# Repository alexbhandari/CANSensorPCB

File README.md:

# Sensor to CAN Bus Remote IO PCB
Many wires in, two wires out. 24 input channels on the board interface with analog and digital sensors. Performs analog to digital to CAN protocol conversion.

## Changelog
| Release | Changes |
| --- | --- |
|  | Pre-release |

## PCB Design

- Microcontroller: RM42L432BPZT
- Input Stage: Filtering, Voltage scaling, Circuit Protection
- Output Stage: 2 Isolated CAN transceivers
- Power: 5V board power, LDO supply creates 3.3V and 1.2V

## [Code Repo](https://github.com/alexbhandari/RM42-CAN-Sensor-Code)

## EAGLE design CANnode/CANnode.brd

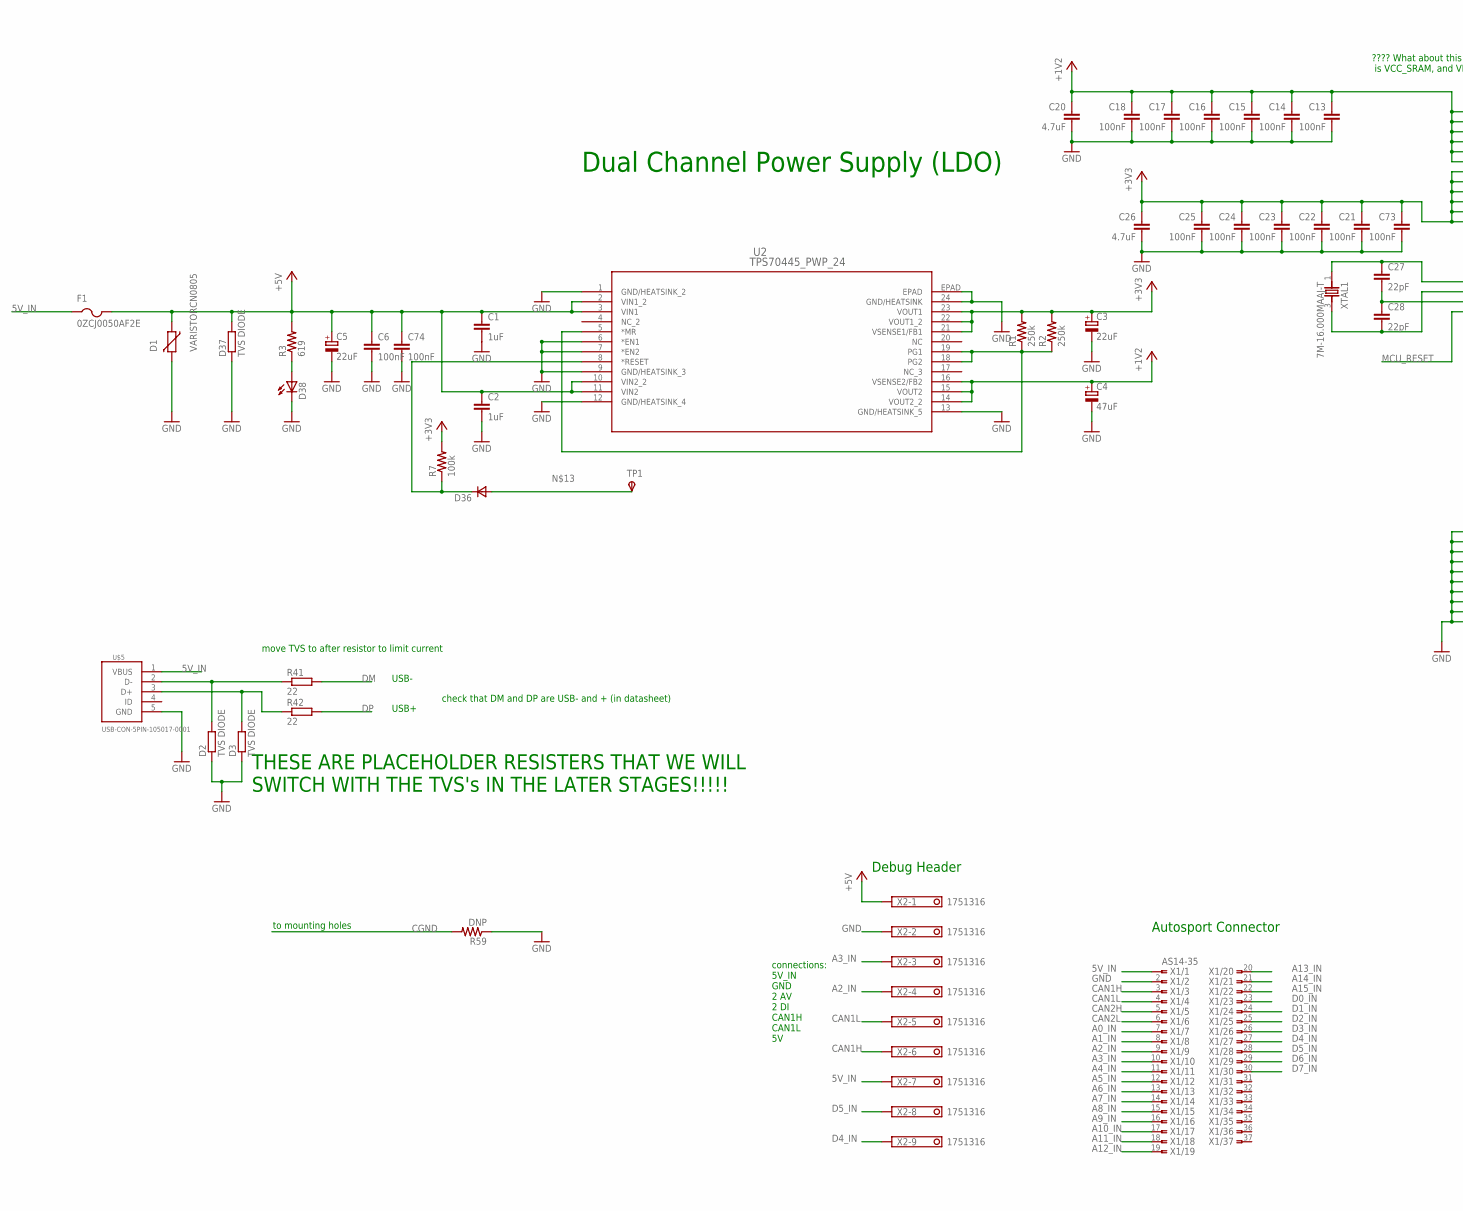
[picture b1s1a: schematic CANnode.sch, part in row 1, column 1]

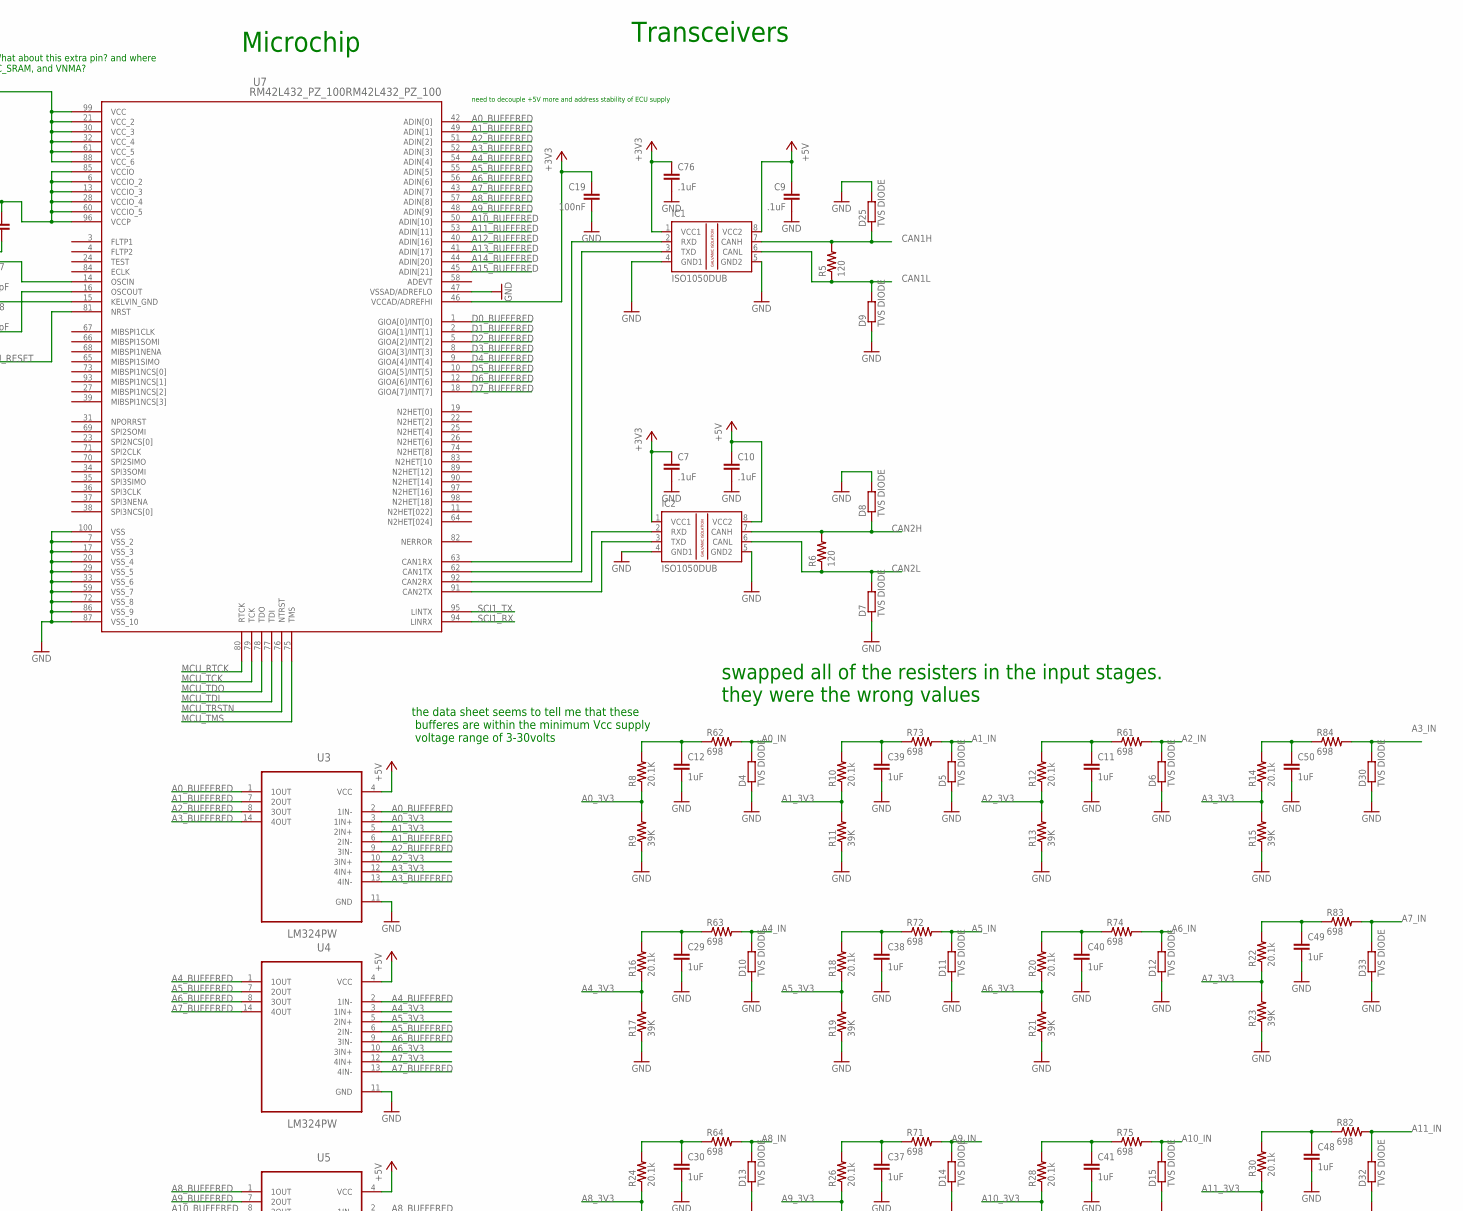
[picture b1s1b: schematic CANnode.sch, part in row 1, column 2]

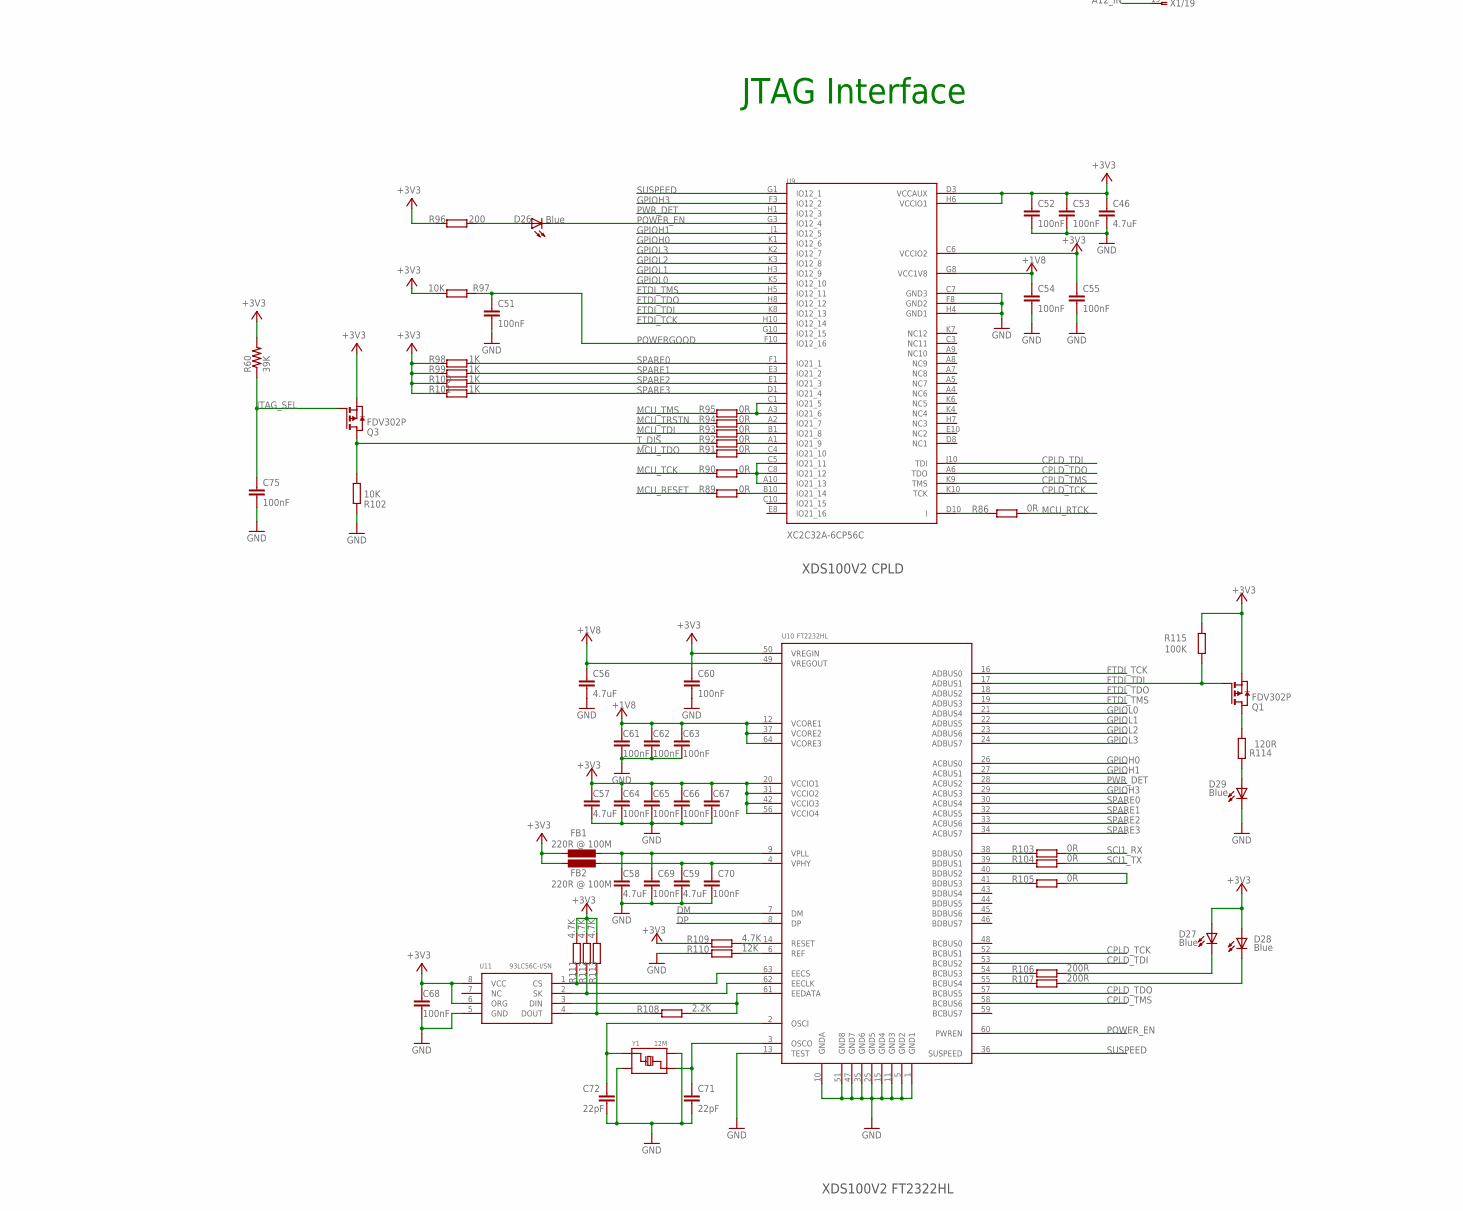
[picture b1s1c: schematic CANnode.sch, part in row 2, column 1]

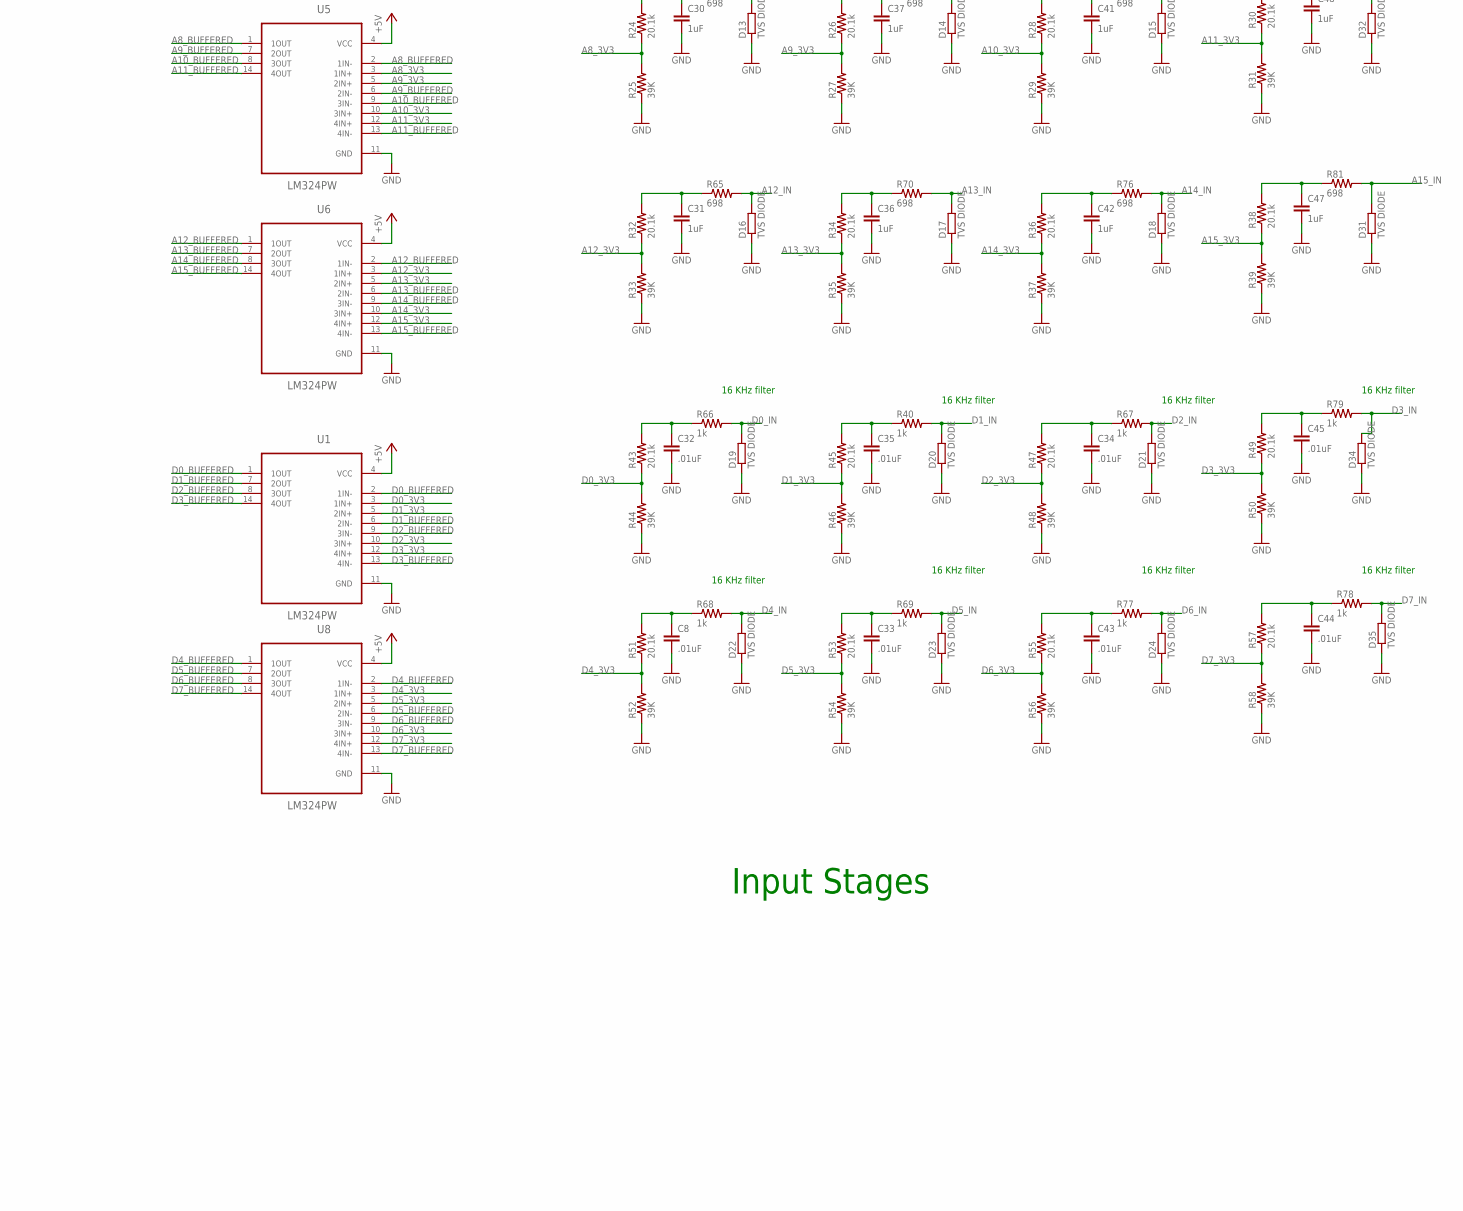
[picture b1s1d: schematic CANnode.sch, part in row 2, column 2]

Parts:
C1, C2, C11, C12, C29, C30, C31, C36, C37, C38, C39, C40, C41, C42, C47, C48, C49, C50: 1uF; C0402
C3, C5: 22uF; CT3528
C4: 47uF; CT3528
C6, C13, C14, C15, C16, C17, C18, C19, C21, C22, C23, C24, C25, C73, C74, C75: 100nF; C0402
C7, C9, C10, C76: .1uF; C0402
C8, C32, C33, C34, C35, C43, C44, C45: .01uF; C0402
C20, C26: 4.7uF; C0805
C27, C28: 22pF; C0402
C46, C56, C57, C58, C59: 4.7uF; 0805
C51, C52, C53, C54, C55, C60, C61, C62, C63, C64, C65, C66, C67, C68, C69, C70: 100nF; 0402
C71, C72: 22pF; 0402
D1: VARISTORCN0805; CT/CN0805
D2, D3, D4, D5, D6, D7, D8, D9, D10, D11, D12, D13, D14, D15, D16, D17, D18, D19, D20, D21, D22, D23, D24, D25, D30, D31, D32, D33, D34, D35, D37: TVS DIODE; R0402
D26, D27, D28, D29: Blue; LED0805
D36: DSOD323; SOD323
D38: LED; SMARTLED-TTW
F1: 0ZCJ0050AF2E; R1206
FB1, FB2: 220R @ 100M; 0805
IC1, IC2: ISO1050DUB; DUB-R-PDSO-G8
Q1, Q3: FDV302P; SOT-23
R1, R2: 250k; R0402
R3: 619; R0402
R5, R6: 120; R0402
R7: 100k; R0402
R8: 20.1K; R0402
R9, R11, R13, R15, R17, R19, R21, R23, R25, R27, R29, R31, R33, R35, R37, R39, R44, R46, R48, R50, R52, R54, R56, R58, R60: 39K; R0402
R10, R12, R14, R16, R18, R20, R22, R24, R26, R28, R30, R32, R34, R36, R38, R43, R45, R47, R49, R51, R53, R55, R57: 20.1k; R0402
R40, R66, R67, R68, R69, R77, R78, R79: 1k; R0402
R41, R42: 22; R0402
R59: DNP; R0402
R61, R62, R63, R64, R65, R70, R71, R72, R73, R74, R75, R76, R81, R82, R83, R84: 698; R0402
R86, R89, R90, R91, R92, R93, R94, R95, R103, R104, R105: 0R; 0402
R96: 200; 0402
R97, R102: 10K; 0402
R98, R99, R100, R101: 1K; 0402
R106, R107: 200R; 0402
R108: 2.2K; 0402
R109, R111, R112, R113: 4.7K; 0402
R110: 12K; 0402
R114: 120R; 0402
R115: 100K; 0402
TP1: TPSB1,27; B1,27
U1, U3, U4, U5, U6, U8: LM324PW; SOP65P640X120-14N
U2: TPS70445_PWP_24; PWP24_4P68X2P4
U7: RM42L432_PZ_100RM42L432_PZ_100; PZ100
U9: XC2C32A-6CP56C; CP56
U10: FT2232HL; LQFP64
U11: 93LC56C-I/SN; SO8
U$5: USB-CON-5PIN-105017-0001; USB-MICRO-MOLEX-105017-0001
X1: AS14-35
X2: 1751316
XTAL1: 7M-16.000MAAJ-T; TXC_7M-16.000MAAJ-T
Y1: 12M; CRYSTAL_3225

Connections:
5V_IN: F1.1, U$5.1 (VBUS), X1.1, X2.7
+1V2: C4.- (+), C13.1, C14.1, C15.1, C16.1, C17.1, C18.1, C20.1, U2.14 (VOUT2_2), U2.15 (VOUT2), U2.16 (VSENSE2/FB2), U7.21 (VCC_2), U7.30 (VCC_3), U7.32 (VCC_4), U7.61 (VCC_5), U7.88 (VCC_6), U7.99 (VCC)
+1V8: C54.1, C56.1, C61.1, C62.1, C63.1, U9.G8 (VCC1V8), U10.12 (VCORE1), U10.37 (VCORE2), U10.49 (VREGOUT), U10.64 (VCORE3)
+3V3: C3.- (+), C7.1, C19.1, C21.1, C22.1, C23.1, C24.1, C25.1, C26.1, C46.1, C52.1, C53.1, C55.1, C57.1, C60.1, C64.1, C65.1, C66.1, C67.1, C68.1, C73.1, C76.1, D27.A, D28.A, FB1.1, FB2.1, IC1.1 (VCC1), IC2.1 (VCC1), Q1.2 (S), Q3.2 (S), R1.2, R2.2, R7.2, R60.2, R96.1, R97.2, R98.1, R99.1, R100.1, R101.1, R109.1, R111.2, R112.2, R113.2, R115.2, U2.21 (VSENSE1/FB1), U2.22 (VOUT1_2), U2.23 (VOUT1), U7.6 (VCCIO_2), U7.13 (VCCIO_3), U7.28 (VCCIO_4), U7.46 (VCCAD/ADREFHI), U7.60 (VCCIO_5), U7.85 (VCCIO), U7.96 (VCCP), U9.C6 (VCCIO2), U9.D3 (VCCAUX), U9.H6 (VCCIO1), U10.20 (VCCIO1), U10.31 (VCCIO2), U10.42 (VCCIO3), U10.50 (VREGIN), U10.56 (VCCIO4), U11.6 (ORG), U11.8 (VCC)
+5V: C1.1, C2.1, C5.- (+), C6.1, C9.1, C10.1, C74.1, D1.1, D37.2, F1.2, IC1.8 (VCC2), IC2.8 (VCC2), R3.2, U1.4 (VCC), U2.2 (VIN1_2), U2.3 (VIN1), U2.10 (VIN2_2), U2.11 (VIN2), U3.4 (VCC), U4.4 (VCC), U5.4 (VCC), U6.4 (VCC), U8.4 (VCC), X2.1
A0_3V3: R8.1, R9.2, U3.3 (1IN+)
A0_BUFFERED: U3.1 (1OUT), U3.2 (1IN-), U7.42 (ADIN[0])
A0_IN: D4.2, R62.2, X1.7
A1_3V3: R10.1, R11.2, U3.5 (2IN+)
A1_BUFFERED: U3.6 (2IN-), U3.7 (2OUT), U7.49 (ADIN[1])
A1_IN: D5.2, R73.2, X1.8
A2_3V3: R12.1, R13.2, U3.10 (3IN+)
A2_BUFFERED: U3.8 (3OUT), U3.9 (3IN-), U7.51 (ADIN[2])
A2_IN: D6.2, R61.2, X1.9, X2.4
A3_3V3: R14.1, R15.2, U3.12 (4IN+)
A3_BUFFERED: U3.13 (4IN-), U3.14 (4OUT), U7.52 (ADIN[3])
A3_IN: D30.2, R84.2, X1.10, X2.3
A4_3V3: R16.1, R17.2, U4.3 (1IN+)
A4_BUFFERED: U4.1 (1OUT), U4.2 (1IN-), U7.54 (ADIN[4])
A4_IN: D10.2, R63.2, X1.11
A5_3V3: R18.1, R19.2, U4.5 (2IN+)
A5_BUFFERED: U4.6 (2IN-), U4.7 (2OUT), U7.55 (ADIN[5])
A5_IN: D11.2, R72.2, X1.12
A6_3V3: R20.1, R21.2, U4.10 (3IN+)
A6_BUFFERED: U4.8 (3OUT), U4.9 (3IN-), U7.56 (ADIN[6])
A6_IN: D12.2, R74.2, X1.13
A7_3V3: R22.1, R23.2, U4.12 (4IN+)
A7_BUFFERED: U4.13 (4IN-), U4.14 (4OUT), U7.43 (ADIN[7])
A7_IN: D33.2, R83.2, X1.14
A8_3V3: R24.1, R25.2, U5.3 (1IN+)
A8_BUFFERED: U5.1 (1OUT), U5.2 (1IN-), U7.57 (ADIN[8])
A8_IN: D13.2, R64.2, X1.15
A9_3V3: R26.1, R27.2, U5.5 (2IN+)
A9_BUFFERED: U5.6 (2IN-), U5.7 (2OUT), U7.48 (ADIN[9])
A9_IN: D14.2, R71.2, X1.16
A10_3V3: R28.1, R29.2, U5.10 (3IN+)
A10_BUFFERED: U5.8 (3OUT), U5.9 (3IN-), U7.50 (ADIN[10])
A10_IN: D15.2, R75.2, X1.17
A11_3V3: R30.1, R31.2, U5.12 (4IN+)
A11_BUFFERED: U5.13 (4IN-), U5.14 (4OUT), U7.53 (ADIN[11])
A11_IN: D32.2, R82.2, X1.18
A12_3V3: R32.1, R33.2, U6.3 (1IN+)
A12_BUFFERED: U6.1 (1OUT), U6.2 (1IN-), U7.40 (ADIN[16])
A12_IN: D16.2, R65.2, X1.19
A13_3V3: R34.1, R35.2, U6.5 (2IN+)
A13_BUFFERED: U6.6 (2IN-), U6.7 (2OUT), U7.41 (ADIN[17])
A13_IN: D17.2, R70.2, X1.20
A14_3V3: R36.1, R37.2, U6.10 (3IN+)
A14_BUFFERED: U6.8 (3OUT), U6.9 (3IN-), U7.44 (ADIN[20])
A14_IN: D18.2, R76.2, X1.21
A15_3V3: R38.1, R39.2, U6.12 (4IN+)
A15_BUFFERED: U6.13 (4IN-), U6.14 (4OUT), U7.45 (ADIN[21])
A15_IN: D31.2, R81.2, X1.22
CAN1H: D25.1, IC1.7 (CANH), R5.2, X1.3, X2.6
CAN1L: D9.2, IC1.6 (CANL), R5.1, X1.4, X2.5
CAN1RX: IC1.2 (RXD), U7.63 (CAN1RX)
CAN1TX: IC1.3 (TXD), U7.62 (CAN1TX)
CAN2H: D8.1, IC2.7 (CANH), R6.2, X1.5
CAN2L: D7.2, IC2.6 (CANL), R6.1, X1.6
CAN2RX: IC2.2 (RXD), U7.92 (CAN2RX)
CAN2TX: IC2.3 (TXD), U7.91 (CAN2TX)
CGND: R59.2
CPLD_TCK: U9.K10 (TCK), U10.52 (BCBUS1)
CPLD_TDI: U9.J10 (TDI), U10.53 (BCBUS2)
CPLD_TDO: U9.A6 (TDO), U10.57 (BCBUS5)
CPLD_TMS: U9.K9 (TMS), U10.58 (BCBUS6)
D0_3V3: R43.1, R44.2, U1.3 (1IN+)
D0_BUFFERED: U1.1 (1OUT), U1.2 (1IN-), U7.1 (GIOA[0]/INT[0])
D0_IN: D19.2, R66.2, X1.23
D1_3V3: R45.1, R46.2, U1.5 (2IN+)
D1_BUFFERED: U1.6 (2IN-), U1.7 (2OUT), U7.2 (GIOA[1]/INT[1])
D1_IN: D20.2, R40.2, X1.24
D2_3V3: R47.1, R48.2, U1.10 (3IN+)
D2_BUFFERED: U1.8 (3OUT), U1.9 (3IN-), U7.5 (GIOA[2]/INT[2])
D2_IN: D21.2, R67.2, X1.25
D3_3V3: R49.1, R50.2, U1.12 (4IN+)
D3_BUFFERED: U1.13 (4IN-), U1.14 (4OUT), U7.8 (GIOA[3]/INT[3])
D3_IN: D34.2, R79.2, X1.26
D4_3V3: R51.1, R52.2, U8.3 (1IN+)
D4_BUFFERED: U7.9 (GIOA[4]/INT[4]), U8.1 (1OUT), U8.2 (1IN-)
D4_IN: D22.2, R68.2, X1.27, X2.9
D5_3V3: R53.1, R54.2, U8.5 (2IN+)
D5_BUFFERED: U7.10 (GIOA[5]/INT[5]), U8.6 (2IN-), U8.7 (2OUT)
D5_IN: D23.2, R69.2, X1.28, X2.8
D6_3V3: R55.1, R56.2, U8.10 (3IN+)
D6_BUFFERED: U7.12 (GIOA[6]/INT[6]), U8.8 (3OUT), U8.9 (3IN-)
D6_IN: D24.2, R77.2, X1.29
D7_3V3: R57.1, R58.2, U8.12 (4IN+)
D7_BUFFERED: U7.18 (GIOA[7]/INT[7]), U8.13 (4IN-), U8.14 (4OUT)
D7_IN: D35.2, R78.2, X1.30
DM: R41.2, U10.7 (DM)
DP: R42.2, U10.8 (DP)
FTDI_TCK: U9.H10 (IO12_14), U10.16 (ADBUS0)
FTDI_TDI: Q1.3 (G), R115.1, U9.K8 (IO12_13), U10.17 (ADBUS1)
FTDI_TDO: U9.H8 (IO12_12), U10.18 (ADBUS2)
FTDI_TMS: U9.H5 (IO12_11), U10.19 (ADBUS3)
GND: C1.2, C2.2, C3.+ (-), C4.+ (-), C5.+ (-), C6.2, C7.2, C8.2, C9.2, C10.2, C11.2, C12.2, C13.2, C14.2, C15.2, C16.2, C17.2, C18.2, C19.2, C20.2, C21.2, C22.2, C23.2, C24.2, C25.2, C26.2, C29.2, C30.2, C31.2, C32.2, C33.2, C34.2, C35.2, C36.2, C37.2, C38.2, C39.2, C40.2, C41.2, C42.2, C43.2, C44.2, C45.2, C46.2, C47.2, C48.2, C49.2, C50.2, C51.2, C52.2, C53.2, C54.2, C55.2, C56.2, C57.2, C58.2, C59.2, C60.2, C61.2, C62.2, C63.2, C64.2, C65.2, C66.2, C67.2, C68.2, C69.2, C70.2, C71.2, C72.2, C73.2, C74.2, C75.2, C76.2, D1.2, D2.1, D3.1, D4.1, D5.1, D6.1, D7.1, D8.2, D9.1, D10.1, D11.1, D12.1, D13.1, D14.1, D15.1, D16.1, D17.1, D18.1, D19.1, D20.1, D21.1, D22.1, D23.1, D24.1, D25.2, D29.C, D30.1, D31.1, D32.1, D33.1, D34.1, D35.1, D37.1, D38.C@1 (C), IC1.4 (GND1), IC1.5 (GND2), IC2.4 (GND1), IC2.5 (GND2), R9.1, R11.1, R13.1, R15.1, R17.1, R19.1, R21.1, R23.1, R25.1, R27.1, R29.1, R31.1, R33.1, R35.1, R37.1, R39.1, R44.1, R46.1, R48.1, R50.1, R52.1, R54.1, R56.1, R58.1, R59.1, R102.1, R110.1, U1.11 (GND), U2.1 (GND/HEATSINK_2), U2.6 (*EN1), U2.7 (*EN2), U2.9 (GND/HEATSINK_3), U2.12 (GND/HEATSINK_4), U2.13 (GND/HEATSINK_5), U2.24 (GND/HEATSINK), U2.EPAD, U3.11 (GND), U4.11 (GND), U5.11 (GND), U6.11 (GND), U7.7 (VSS_2), U7.17 (VSS_3), U7.20 (VSS_4), U7.29 (VSS_5), U7.33 (VSS_6), U7.47 (VSSAD/ADREFLO), U7.59 (VSS_7), U7.72 (VSS_8), U7.86 (VSS_9), U7.87 (VSS_10), U7.100 (VSS), U8.11 (GND), U9.C7 (GND3), U9.F8 (GND2), U9.H4 (GND1), U10.1 (GND1), U10.5 (GND2), U10.10 (GNDA), U10.11 (GND3), U10.13 (TEST), U10.15 (GND4), U10.25 (GND5), U10.35 (GND6), U10.47 (GND7), U10.51 (GND8), U11.5 (GND), U$5.5 (GND), X1.2, X2.2, Y1.P$2, Y1.P$4
GPIOH0: U9.K1 (IO12_6), U10.26 (ACBUS0)
GPIOH1: U9.J1 (IO12_5), U10.27 (ACBUS1)
GPIOH3: U9.F3 (IO12_2), U10.29 (ACBUS3)
GPIOL0: U9.K5 (IO12_10), U10.21 (ADBUS4)
GPIOL1: U9.H3 (IO12_9), U10.22 (ADBUS5)
GPIOL2: U9.K3 (IO12_8), U10.23 (ADBUS6)
GPIOL3: U9.K2 (IO12_7), U10.24 (ADBUS7)
JTAG_SEL: C75.1, Q3.3 (G), R60.1
MCU_RESET: R89.1, U7.81 (NRST)
MCU_RTCK: R86.2, U7.80 (RTCK)
MCU_TCK: R90.1, U7.79 (TCK)
MCU_TDI: R93.1, U7.77 (TDI)
MCU_TDO: R91.1, U7.78 (TDO)
MCU_TMS: R95.1, U7.75 (TMS)
MCU_TRSTN: R94.1, U7.76 (NTRST)
unnamed: R1.1, R2.1, U2.5 (*MR), U2.18 (PG2), U2.19 (PG1)
unnamed: D38.A@1 (A), R3.1
unnamed: C58.1, C69.1, FB1.2, U10.9 (VPLL)
unnamed: C59.1, C70.1, FB2.2, U10.4 (VPHY)
unnamed: R110.2, U10.6 (REF)
unnamed: R109.2, U10.14 (RESET)
unnamed: C72.1, U10.2 (OSCI), Y1.P$3
unnamed: D36.1 (C), R7.1, U2.8 (*RESET)
unnamed: D36.2 (A), TP1.TP
unnamed: C27.2, C28.1, U7.15 (KELVIN_GND)
unnamed: C27.1, U7.14 (OSCIN), XTAL1.1
unnamed: C71.1, U10.3 (OSCO), Y1.P$1
unnamed: C28.2, U7.16 (OSCOUT), XTAL1.3
unnamed: R111.1, U10.63 (EECS), U11.1 (CS)
unnamed: R112.1, U10.62 (EECLK), U11.2 (SK)
unnamed: D2.2, R41.1, U$5.2 (D-)
unnamed: D3.2, R42.1, U$5.3 (D+)
unnamed: D26.A, R96.2
unnamed: R108.2, U10.61 (EEDATA), U11.3 (DIN)
unnamed: R108.1, R113.1, U11.4 (DOUT)
unnamed: R106.1, U10.54 (BCBUS3)
unnamed: R107.1, U10.55 (BCBUS4)
unnamed: R103.1, U10.38 (BDBUS0)
unnamed: R104.1, U10.39 (BDBUS1)
unnamed: R95.2, U9.A3 (IO21_6), U9.C1 (IO21_5)
unnamed: Q1.1 (D), R114.2
unnamed: R94.2, U9.A2 (IO21_7)
unnamed: R93.2, U9.B1 (IO21_8)
unnamed: R92.2, U9.A1 (IO21_9)
unnamed: R91.2, U9.C4 (IO21_10)
unnamed: R90.2, U9.A10 (IO21_13), U9.C5 (IO21_11), U9.C8 (IO21_12)
unnamed: R89.2, U9.B10 (IO21_14)
unnamed: D29.A, R114.1
unnamed: R105.2, U10.40 (BDBUS2)
unnamed: R105.1, U10.41 (BDBUS3)
unnamed: R86.1, U9.D10 (I)
unnamed: D27.C, R106.2
unnamed: D28.C, R107.2
unnamed: C11.1, R12.2, R61.1
unnamed: C12.1, R8.2, R62.1
unnamed: C29.1, R16.2, R63.1
unnamed: C30.1, R24.2, R64.1
unnamed: C31.1, R32.2, R65.1
unnamed: C32.1, R43.2, R66.1
unnamed: C8.1, R51.2, R68.1
unnamed: C33.1, R53.2, R69.1
unnamed: C35.1, R40.1, R45.2
unnamed: C36.1, R34.2, R70.1
unnamed: C37.1, R26.2, R71.1
unnamed: C38.1, R18.2, R72.1
unnamed: C39.1, R10.2, R73.1
unnamed: C40.1, R20.2, R74.1
unnamed: C41.1, R28.2, R75.1
unnamed: C42.1, R36.2, R76.1
unnamed: C34.1, R47.2, R67.1
unnamed: C43.1, R55.2, R77.1
unnamed: C44.1, R57.2, R78.1
unnamed: C45.1, R49.2, R79.1
unnamed: C47.1, R38.2, R81.1
unnamed: C48.1, R30.2, R82.1
unnamed: C49.1, R22.2, R83.1
unnamed: C50.1, R14.2, R84.1
POWERGOOD: C51.1, R97.1, U9.F10 (IO12_16)
POWER_EN: D26.C, U9.G3 (IO12_4), U10.60 (PWREN)
PWR_DET: U9.H1 (IO12_3), U10.28 (ACBUS2)
SCI1_RX: R103.2, U7.94 (LINRX)
SCI1_TX: R104.2, U7.95 (LINTX)
SPARE0: R98.2, U9.F1 (IO21_1), U10.30 (ACBUS4)
SPARE1: R99.2, U9.E3 (IO21_2), U10.32 (ACBUS5)
SPARE2: R100.2, U9.E1 (IO21_3), U10.33 (ACBUS6)
SPARE3: R101.2, U9.D1 (IO21_4), U10.34 (ACBUS7)
SUSPEED: U9.G1 (IO12_1), U10.36 (SUSPEED)
T_DIS: Q3.1 (D), R92.1, R102.2

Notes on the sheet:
Dual Channel Power Supply (LDO)
Transceivers
Microchip
need to decouple +5V more and address stability of ECU supply
???? What about this extra pin? and where is VCC_SRAM, and VNMA?
move TVS to after resistor to limit current
THESE ARE PLACEHOLDER RESISTERS THAT WE WILL SWITCH WITH THE TVS's IN THE LATER STAGES!!!!!
Input Stages
swapped all of the resisters in the input stages. they were the wrong values
the data sheet seems to tell me that these bufferes are within the minimum Vcc supply voltage range of 3-30volts
16 KHz filter
Debug Header
Autosport Connector
XDS100V2 CPLD
XDS100V2 FT2322HL
JTAG Interface
USB-
USB+
check that DM and DP are USB- and + (in datasheet)
connections: 5V_IN GND 2 AV 2 DI CAN1H CAN1L 5V
to mounting holes

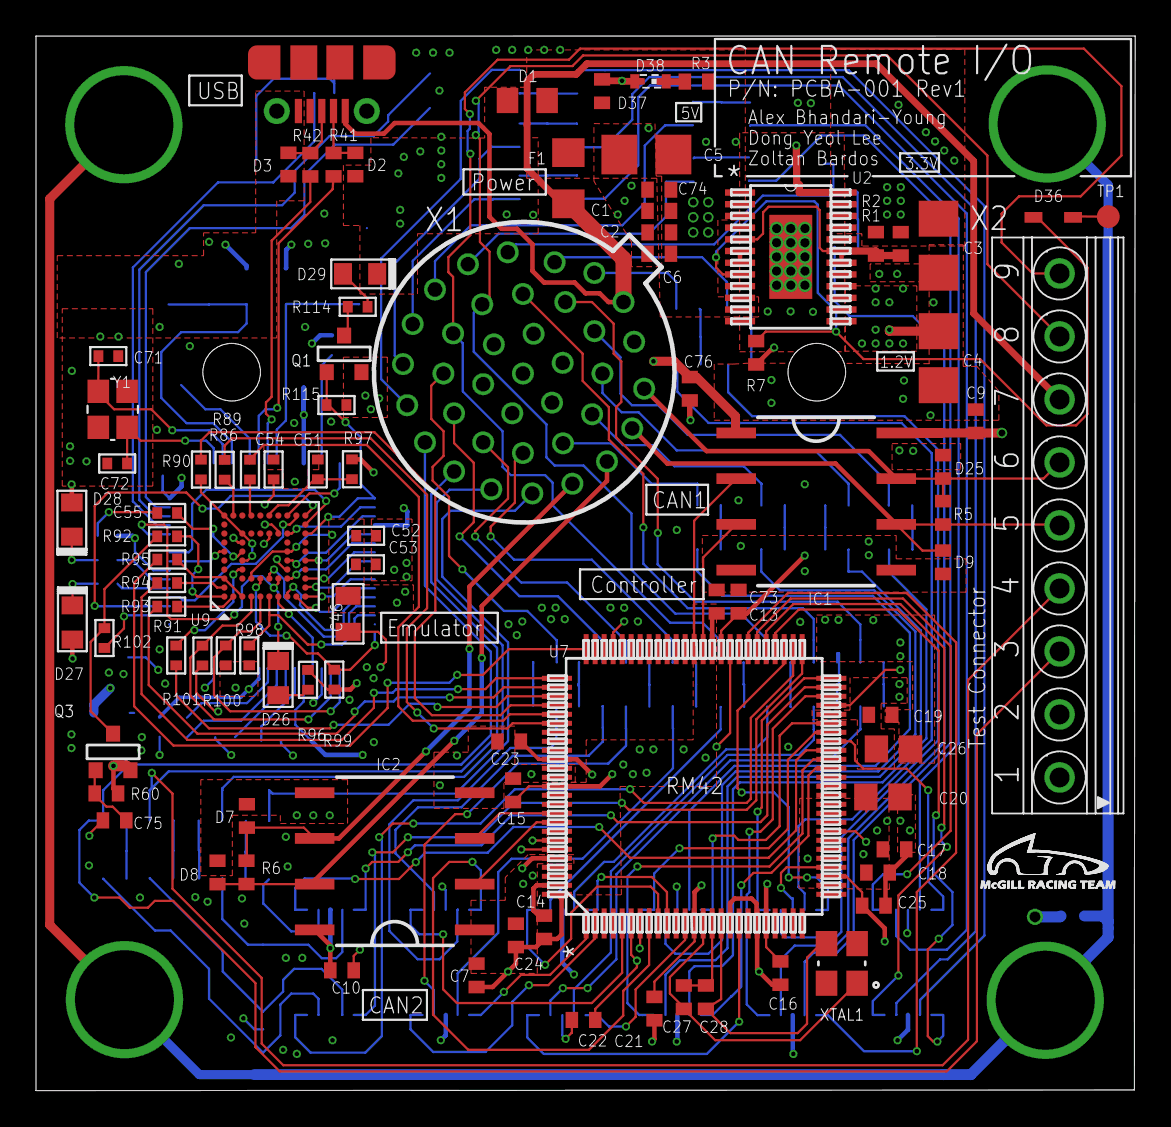
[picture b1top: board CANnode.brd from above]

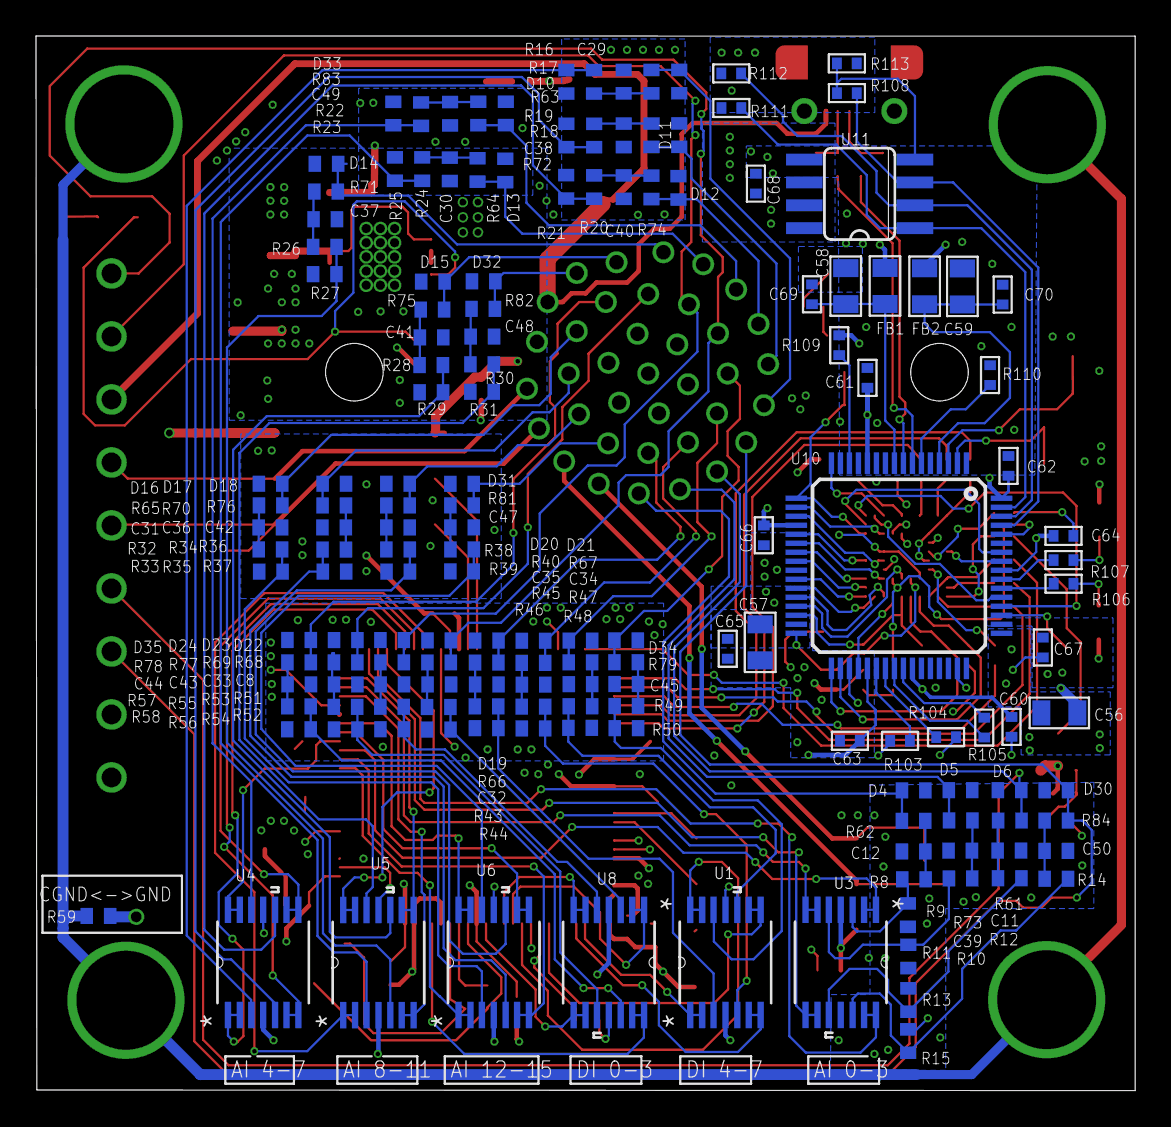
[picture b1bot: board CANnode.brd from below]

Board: 4 copper layers, 61.1 x 58.6 mm, 248 parts (157 on the bottom side), 184 nets.

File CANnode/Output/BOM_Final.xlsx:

Item # | Ref Des | Qty | Manufacturer | Mfg Part # | Description | Package | Type | Your Instructions | Value | Device
 | C8, C32, C33, C34, C35, C43, C44, C45 | 8 | Murata Electronics North America | GRM155R71H103KA88D | CAP CER 10000PF 50V X7R 0402 | 0402 | SMD |  | .01uF | CAP0402
 | C7, C9, C10, C76 | 4 | Murata Electronics North America | GRM155R71C104JA88D | CAP CER 0.1UF 16V X7R 0402 | 0402 | SMD |  | .1uF | CAP0402
 | R86, R89, R90, R91, R92, R93, R94, R95, R103, R104, R105 | 11 | Yageo | RC0402JR-070RL | RES SMD 0.0OHM JUMPER 1/16W 0402 | 0402 | SMD |  | 0R | RES0402
 | F1 | 1 | Bel Fuse Inc. | 0ZCJ0050AF2E | PTC RESTTBLE 0.50A 24V CHIP 1206 | 1206 | SMD |  | 0ZCJ0050AF2E | PTCFUSE-1206
 | R7, R115 | 2 | Yageo | RC0402FR-07100KL | RES SMD 100K OHM 1% 1/16W 0402 | 0402 | SMD |  | 100K | RES0402
 | C13, C14, C15, C16, C17, C18, C19, C21, C22, C23, C24, C25, C73, C75, C51, C52,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 | 32 | Murata Electronics North America | GRM155R71C104JA88D | CAP CER 0.1UF 16V X7R 0402 | 0402 | SMD |  | 100nF | CAP0402
 | R97, R102 | 2 | Yageo | RC0402JR-0710KL | RES SMD 10K OHM 5% 1/16W 0402 | 0402 | SMD |  | 10K | RES0402
 | R5,R6,R114 | 3 | Vishay Dale | CRCW0402120RJNEDHP | RES SMD 120 OHM 5% 1/5W 0402 | 0402 | SMD |  | 120R | RES0402
 | R110 | 1 | Yageo | RC0402JR-0712KL | RES SMD 12K OHM 5% 1/16W 0402 | 0402 | SMD |  | 12K | RES0402
 | Y1 | 1 | TXC | 7M-12.000MEEQ-T | Crystal 12MHZ | 3.2*2.5mm | SMD |  | 12M | CRYSTAL-SMD
 | X2 | 1 | Phoenix Contact | 1751316 | CONN TERM BLOCK 9POS 3.5MM | 32*7.3mm | Through Hole |  | 1751316 | 1751316
 | R40, R66, R67, R68, R69, R77, R78, R79, R98, R99, R100, R101 | 12 | Yageo | RC0402FR-071KL | RES SMD 1K OHM 1% 1/16W 0402 | 0402 | SMD |  | 1K | RES0402
 | C1, C2,C11, C12, C29, C30, C31, C36, C37, C38, C39, C40, C41, C42, C47, C48, C4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 | 18 | Murata Electronics North America | GRM155R60J105KE19D | CAP CER 1UF 6.3V X5R 0402 | 0402 | SMD |  | 1uF | CAP0402
 | R108 | 1 | Panasonic Electronic Components | ERJ-2GEJ222X | RES SMD 2.2K OHM 5% 1/10W 0402 | 0402 | SMD |  | 2.2K | RES0402
 | R8,R10, R12, R14, R16, R18, R20, R22, R24, R26, R28, R30, R32, R34, R36, R38, R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 | 24 | Susumu | RR0510P-203-D | RES SMD 20K OHM 0.5% 1/16W 0402 | 0402 | SMD |  | 20K | RES0402
 | R96,R106, R107 | 3 | Panasonic Electronic Components | ERJ-2RKF2000X | RES SMD 200 OHM 1% 1/10W 0402 | 0402 | SMD |  | 200 | RES0402
 | R41, R42 | 2 | Yageo | RC0402FR-0722RL | RES SMD 22 OHM 1% 1/16W 0402 | 0402 | SMD |  | 22 | RES0402
 | FB1, FB2 | 2 | MURATA | BLM21PG221SN1D | Ferrite Bead | 0805 | SMD |  | 220R @ 100M | INDUCTOR
 | C27, C28, C71, C72 | 4 | Johanson Technology Inc. | 500R07S220JV4T | CAP CER 22PF 50V NP0 0402 | 0402 | SMD |  | 22pF | CAP0402
 | C3, C5 | 2 | AVX Corporation | F920J226MPA | CAP TANT 22UF 6.3V 20% 0805 | 0805 | SMD |  | 22uF | CAP0805
 | R3 | 1 | Samsung Electro-Mechanics America, Inc. | RC1005F6190CS | RES SMD 619 OHM 1% 1/16W 0402 | 0402 | SMD |  | 619 | RES0402
 | R1, R2 | 2 | Yageo | RC0402FR-07249KL | RES SMD 249K OHM 1% 1/16W 0402 | 0402 | SMD |  | 250k | RES0402
 | R9, R11, R13, R15, R17, R19, R21, R23, R25, R27, R29, R31, R33, R35, R37, R39, 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 | 25 | Susumu | RR0510P-393-D | RES SMD 39K OHM 0.5% 1/16W 0402 | 0402 | SMD |  | 39K | RES0402
 | R109, R111, R112, R113 | 4 | Yageo | RC0402JR-074K7L | RES SMD 4.7K OHM 5% 1/16W 0402 | 0402 | SMD |  | 4.7K | RES0402
 | C20, C26, C46, C56, C57, C58, C59 | 7 | Taiyo Yuden | LMK212BJ475KD-T | CAP CER 4.7UF 10V X5R 0805 | 0805 | SMD |  | 4.7uF | CAP0805
 | C4 | 1 | Murata Electronics North America | GRM155R71E473KA88D | CAP CER 0.047UF 25V X7R 0402 | 0402 | SMD |  | 47uF | CAP0402
 | R61, R62, R63, R64, R65, R70, R71, R72, R73, R74, R75, R76, R81, R82, R83, R84 | 16 | Panasonic Electronic Components | ERJ-2RKF6980X | RES SMD 698 OHM 1% 1/10W 0402 | 0402 | SMD |  | 698 | RES0402
 | XTAL1 | 1 | TXC | 7M-16.000MAAJ-T | Crystal 16MHZ | 3.2*2.5mm | SMD |  | 7M-16.000MAAJ-T | CRYSTAL-SMD
 | U11 | 1 | Microchip Technology | 93LC56C-I/SN | IC EEPROM 2KBIT 3MHZ 8SOIC | 8-SOIC | SMD |  | 93LC56C-I/SN | 93LC56C-I/SN
 | X1 | 1 | Deutch | AS214-35-PN | Autosport connector |  |  | do not populate | AS14-35 | AS14-35
 | R59 | 1 |  |  |  |  |  |  | DNP | RES0402
 | Q1, Q3 | 2 | Fairchild Semiconductor | FDV302P | MOSFET P-CH 25V 120MA SOT-23 | SOT-23 | SMD |  | FDV302P | PMOSSOT23
 | U10 | 1 | FTDI, Future Technology Devices International Ltd | FT2232HL | IC USB HS DUAL UART/FIFO 64-LQFP | 64-LQFP | SMD |  | FT2232HL | FT2232HL
 | IC1, IC2 | 2 | Texas Instruments | ISO1050DUBR | IC TXRX CAN 5V 8SOP | 8-SOP | SMD |  | ISO1050DUB | ISO1050DUB
 | U1, U3, U4, U5, U6, U8 | 6 | Texas Instruments | LM324PW | IC OPAMP GP 1.2MHZ 14TSSOP | 14-TSSOP | SMD |  | LM324PW | LM324PW
 | U7 | 1 | Texas Instruments | RM42L432BPZT | IC MCU 16BIT 384KB FLASH 100LQFP | 100-LQFP | SMD |  | RM42L432_PZ_100RM42L432_PZ_100 | RM42L432_PZ_100RM42L432_PZ_100
 | U2 | 1 | Texas Instruments | TPS70445PWP | IC REG LDO 3.3V/1.2V 24HTSSOP | 24-HTSSOP | SMD |  | TPS70445_PWP_24 | TPS70445_PWP_24
 | D2, D3, D4, D5, D6, D7, D8, D9, D10, D11, D12, D13, D14, D15, D16, D17, D18, D1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 | 30 | Semtech Corporation | UCLAMP1201P.TCT | TVS DIODE 12VWM 25VC 2SLP | 0402 | SMD |  | TVS DIODE | TVS0402
 | U$5 | 1 | Molex, LLC | 1050170001 | USB - micro B Receptacle Connector 5 Position Board Cutout, Surface Mount, Righ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 | 7.5*5.0mm | SMD |  | USB-CON-5PIN-105017-0001 | USB-CON-5PIN-105017-0001
 | U9 | 1 | Xilinx Inc. | XC2C32A-6CP56C | IC CPLD 32MC 5.5NS 56BGA | 56-LFBGA, CSPBGA | SMD |  | XC2C32A-6CP56C | XC2C32A-6CP56C | possibe replacment: XC2C64A-7CPG56I
 | D26, D27 | 1 | Lite-On Inc. | LTST-C170TBKT | LED BLUE CLEAR 0805 SMD | 0805 | SMD |  | BLUE | CHIP-LED-BLUE
 | D28 | 1 | Lite-On Inc. | LTW-170TK | LED WHITE 0805 SMD | 0805 | SMD |  | YELLOW | CHIP-LED-YELLOW
 | D29 | 1 | Kingbright | APHCM2012ZGC-F01 | LED GREEN CLEAR 0805 SMD | 0805 | SMD |  | GREEN | CHIP-LED-GREEN
 | D36 | 1 | ON Semiconductor | NSR0320MW2T1G | DIODE SCHOTTKY 20V 1A SOD323 | SOD323 | SMD |  | 20V | DSOD323
 | D38 | 1 | Kingbright | APG1005VGC-T-5MAV | LED GREEN CLEAR 0402 SMD | 0402 | SMD |  | GREEN | CHIP-LED-GREEN
 | D37 | 1 | Comchip Technology | CPDQR5V0USP-HF | DIODE ESD 5V UNIDIR 0402 |  | SMD |  | 5V | Zener
 | D1 | 1 | Littelfuse Inc. | V5.5MLA0805NH | VARISTOR 7.1V 120A 0805 |  | SMD |  | 5.5V | Varistor

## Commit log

2015-10-03 Added eagle schematics - power supply circuit started
2015-11-20 Zoltan's compiling CAN example project
    builds and flashes, have not tested that CAN is working
2015-11-20 Circuit design update
2015-11-23 sciSend working
2015-11-23 sciSend working with CAN but some anomalies
    Transmits and receives on first try with full circuit wired on
    breadboard. After removing CAN2 it stalls waiting for transmit
    confirmation for the first byte.
2015-11-24 changed folder name
2015-11-25 Added resistor dividers + buffers for analog inputs
2016-01-14 Changes in input stage: copy and paste 3 times
2016-01-14 Aligned to make the circuit look better
2016-01-14 Changed TMS chip to RM42
2016-01-16 added capacitor banks, moved the trancievers to look nicer
2016-01-16 Rearranged pins for RM42
2016-01-16 Ignore Lock Files
2016-01-16 added real capacitors by hand, grouded VSS pins, started witinf VCC pins
2016-01-16 Added a crystal
2016-01-16 Wired power and CAN up
2016-01-18 Added micro-usb part (not complete)
2016-01-20 Wired analog and digital inputs to RM42
2016-01-21 zoltan working on CAN, added tranciever
2016-01-22 changed all the resisters in the input stage, removed a reduddant section, added headers, removed CAN caps, fixed grounds
2016-01-22 Added TVS diodes to input stages. Cleaned up schematic. Added JTAG circuitry.
2016-01-22 Changed 22R to 22, component names and rearranged wires
2016-01-24 Added include path. Cleaned project.
2016-01-26 Added ADC support via Halcogen
2016-01-26 started layout experiment. its difficult and weird first attempt.
2016-01-29 Placed chips on the board (except for resistors, capacitors and diodes)
2016-01-29 Placed digital input components on the board
2016-01-30 Started placing analog input components
2016-01-31 Placed analog input components on the board
2016-02-03 Moved input components to bottom layer and wired
2016-02-03 more layout and new files and such
2016-02-04 moved buffers to the bottom layers and put more components on the board
2016-02-04 Altium Import
2016-02-04 Deleted extra traces on the bottom layer that appear to be artifacts of the import.
2016-02-04 Updated git ignore
2016-02-05 Finished putting all the components on the board (but still needs to be more organized)
2016-02-07 Rearranged components
2016-02-10 played with vias and routing
2016-02-11 Added another layer (Power)
2016-02-14 Connected +5V
2016-02-15 Connected +1V2
2016-02-15 Connected +1V8
2016-02-16 Connected +3V3
2016-02-17 Fished wiring+3V3 and started wiring can components
2016-02-17 Modifications on routing powers
2016-02-17 Moved a LOT OF STUFF: SQUISH
2016-02-18 Reduced the board even more (changes on top layer)
2016-02-18 Focused on power positioning and some routing. Finished 5V_IN from connector and +5V to power supply. Placed caps for 3V3 and 1V2 around RM42. Placed and routed crystal.
2016-02-18 Reduced the board size to 2.7inch*2.4inch (not done)
2016-02-19 Reduced the size to 2.33inch*2.39inch
2016-02-20 Reduced the size to 2.33 x 2.27
2016-02-21 Routed CAN and RM42
2016-02-23 Board size fixed. Bottom layer changed.
2016-02-24 Started routing JTAG
2016-02-25 Routing two JTAG chips (complicated and lots of vias)
2016-02-25 Added missing JTAG connection to MCU
2016-02-25 added comment to move TVS after resistor on USB input
2016-02-26 Routed JTAG. Board size is reduced to 2.26x2.27.
    The fuse is put outside of the board for the future replacement.
2016-02-27 Added PTC fuse
2016-02-28 Connected JTAG to RM42. Board size reduced to 2.17x2.28. Relocated power supply components
2016-02-28 Started locating input stages
2016-02-29 A lot of work on input stages (not finished yet)
2016-03-01 More work on input stages
2016-03-02 Routed buffers
2016-03-03 Finished routing input stages
2016-03-03 Started drawing power planes
2016-03-04 Continued working on power planes
2016-03-05 Routed +5V, +1V8, +1V2
2016-03-05 Started grounding input stages
2016-03-06 Finished grounding bottom layer. Started routing +3V3
2016-03-06 Finished routing bottom layer
2016-03-07 Finished grounding and powering. Whole board needs to be reviewed
2016-03-08 Routed missing JTAG to MCU connections
2016-03-08 Changed mounting holes to big vias. Move the origin of the board.
2016-03-09 Added CAM job and preliminary gerbers
2016-03-09 added connector
2016-03-09 Started routing Debug headers
2016-03-09 Finished Debug headers
2016-03-10 Updated silkscreen, some ground pours, added pullup on jtag select line.
2016-03-10 Layout changes.
2016-03-10 Modified 5V pour for CAN
2016-03-10 Routed SCI1_TX & RX
2016-03-10 Worked on DRC errors. Solved Polygon errors and overlapping erors. Reduced via sizes for some connections.
2016-03-11 Post Bei review. USB runs closer together. CAN and JTAG need to be rerouted a bit.
2016-03-11 Routed TCK without vias
2016-03-11 Moved LEDs from bottom to top layer
2016-03-11 Tidying silkscreen on bottom layer
2016-03-11 Updated input protection.
2016-03-11 BOM finished except for res and cap part numbers. Need to check DNPs, 0 ohms, and crystals.
2016-03-11 Regenerated gerbers
2016-03-11 Moved board origin to bottom left corner of board. Moved mounting holes inward for better mechanical strength.
2016-03-11 Fixed an acute angle and increased size of ground trace on RM42
2016-03-11 Updated BOM
2016-03-11 Final review. Solved overlapping drc errors
2016-03-11 changed power caps to 0805. working on BOM
2016-03-11 CAN resistors
2016-03-11 Connected C4 to +1v2
2016-03-11 Finished BOM
2016-03-11 Renamed internal copper layers
2016-03-11 Submittable BOM
2016-03-13 Added MRT Logo
2016-03-14 Updated Silk
2016-03-14 added job
2016-03-14 Regenerated silk screen gerbers
2016-03-17 Revert "Submittable BOM"
    This reverts commit d765dbeff16fbf7401db7d2f9c843ce674e1691c.
2016-03-17 Revert "Revert "Submittable BOM""
    This reverts commit ef0a1a6dea697aed33fd8ed38d90974a342e9a82.
2016-03-17 Revert back to Submittable BOM
2016-03-17 Removed built by text
2016-03-17 housekeeping
2016-03-17 deleted board to be merged
2016-03-17 Regenerated gerbers 3D view looks good
2016-03-17 Updated jobs
2016-03-17 Changed via sizes to 10 mils
2016-03-18 added logo
2016-03-18 gerbers
2016-03-19 Create Gerbers_2
2016-03-19 Create test
2016-03-19 Added new gerber files
2016-03-19 Added files via upload
2016-04-14 Cleaning up
2016-04-14 added photos

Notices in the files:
parts and their libraries:
GeekAmmo: Licensing:Creative Commons ShareAlike 4.0 International - https://creativecommons.org/licenses/by-sa/4.0
